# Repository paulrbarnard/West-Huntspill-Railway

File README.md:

# West-Huntspill-Railway
This is a project for the West Huntspill Model Railway

https://en-gb.facebook.com/pages/category/Arts---Entertainment/West-Huntspill-Railway-246006162152817/

WHR run model live steam and electric locos on their track.

This project was to replace the old signal system with something a little more flexible
The key modules are the SignalBox which provides the control logic with a track display
and the sensor/lights module that detects the trains and switches the signal lights.

PCB layouts are included in the PCB folder in KiCAD format. Parts lists and UK suppliers are in the excel files in the PCB section.

An overview manual is contained in the .docx file

The PCB layouts and code are released free of charge and can be used or modified in any way you like.

No expressed or implied warrenty or gaurentee is made.

If you like the project and make use of it consider a donation to the West Huntspill Model Railway

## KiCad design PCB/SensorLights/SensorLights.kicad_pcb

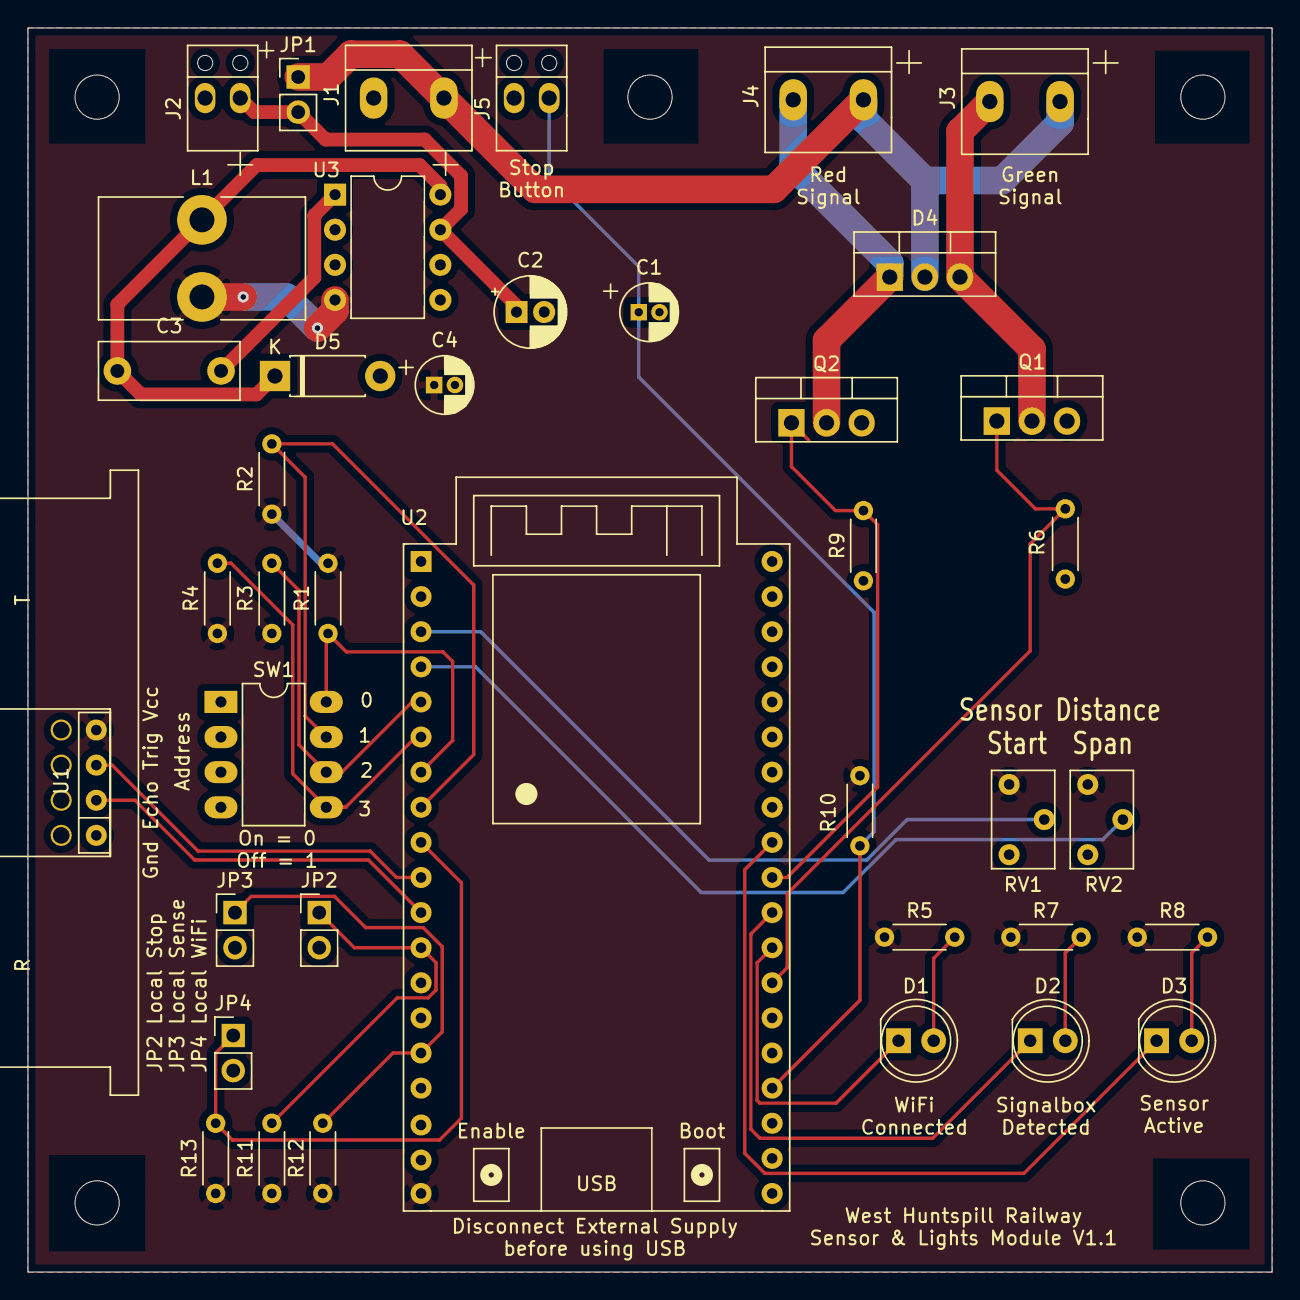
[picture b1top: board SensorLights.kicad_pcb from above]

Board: 2 copper layers, 90.0 x 90.0 mm, 40 parts (0 on the bottom side), 28 nets.

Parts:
C1, C4: 68uF; C_Radial_D4.0mm_H7.0mm_P1.50mm
C2: 100uF; CP_Radial_D5.0mm_P2.00mm
C3: 10nF; C_Rect_L10.0mm_W4.0mm_P7.50mm_MKS4
D1: Yellow; LED_D5.0mm
D2: Green; LED_D5.0mm
D3: Red; LED_D5.0mm
D4: DSSK50-01A; TO-220-3_Vertical
D5: 1N5819RL; D_DO-41_SOD81_P7.62mm_Horizontal
J1: Signal Power; 2WayTerminalStrip_5mm
J2: Board Power; 2WayScrewTerminal_2.54
J3: Green Signal; 2WayTerminalStrip_5mm
J4: Red Signal; 2WayTerminalStrip_5mm
J5: Manual Stop; 2WayScrewTerminal_2.54
JP1: Jumper; PinHeader_1x02_P2.54mm_Vertical
JP2: Local Stop; PinHeader_1x02_P2.54mm_Vertical
JP3: Local Sense; PinHeader_1x02_P2.54mm_Vertical
JP4: Local WiFi; PinHeader_1x02_P2.54mm_Vertical
L1: 47uH; L_Toroid_Vertical_L14.7mm_W8.6mm_P5.58mm_Pulse_KM-1
Q1, Q2: RFP50N06LE; TO-220-3_Vertical
R1, R2, R3, R4, R6, R9, R11, R12, R13: 10K; R_Axial_DIN0204_L3.6mm_D1.6mm_P5.08mm_Horizontal
R5, R8: 1K2; R_Axial_DIN0204_L3.6mm_D1.6mm_P5.08mm_Horizontal
R7, R10: 470R; R_Axial_DIN0204_L3.6mm_D1.6mm_P5.08mm_Horizontal
RV1, RV2: 10K; Potentiometer_TT_M64W
SW1: Address; DIP_SW-8_W7.62mm_LongPads
U1: HC-SR04
U2: ESP32_DevKit_V4; esp32_devkit_v4
U3: LM2675N-5; DIP-8_W7.62mm

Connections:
+5V: C4.1, L1.2, R1.1, R2.1, R3.1, R4.1, R5.1, R7.1, R8.1, R10.1, R11.1, R12.1, R13.1, RV1.1, RV2.1, U1.4, U2.19, U3.4
/5V Supply/6V-24V: C2.1, J2.2, JP1.2, U3.7
GND: C1.2, C2.2, C4.2, D5.2, J1.1, J2.1, J5.1, JP2.2, JP3.2, JP4.2, Q1.3, Q2.3, R6.2, R9.2, RV1.3, RV2.3, SW1.1, SW1.2, SW1.3, SW1.4, U1.1, U2.14, U2.32, U2.38, U3.6
unnamed: C3.1, D5.1, L1.1, U3.8
unnamed: C3.2, U3.1
unnamed: D1.1, U2.27
unnamed: D1.2, R5.2
unnamed: D2.1, U2.28
unnamed: D2.2, R7.2
unnamed: D3.1, U2.30
unnamed: D3.2, R8.2
unnamed: D4.1, J4.1, Q2.2
unnamed: D4.3, J3.1, Q1.2
unnamed: JP2.1, R11.2, U2.12
unnamed: JP3.1, R12.2, U2.15
unnamed: Q1.1, R6.1, U2.26
unnamed: Q2.1, R9.1, U2.29
unnamed: R1.2, SW1.8, U2.7
unnamed: R2.2, SW1.7, U2.8
unnamed: R3.2, SW1.6, U2.5
unnamed: R4.2, SW1.5, U2.6
unnamed: RV1.2, U2.3
unnamed: RV2.2, U2.4
unnamed: U1.2, U2.11
unnamed: U1.3, U2.10
SignalPower: D4.2, J1.2, J3.2, J4.2, JP1.1
Stop: C1.1, J5.2, R10.2, U2.23
lWiFi: JP4.1, R13.2, U2.9

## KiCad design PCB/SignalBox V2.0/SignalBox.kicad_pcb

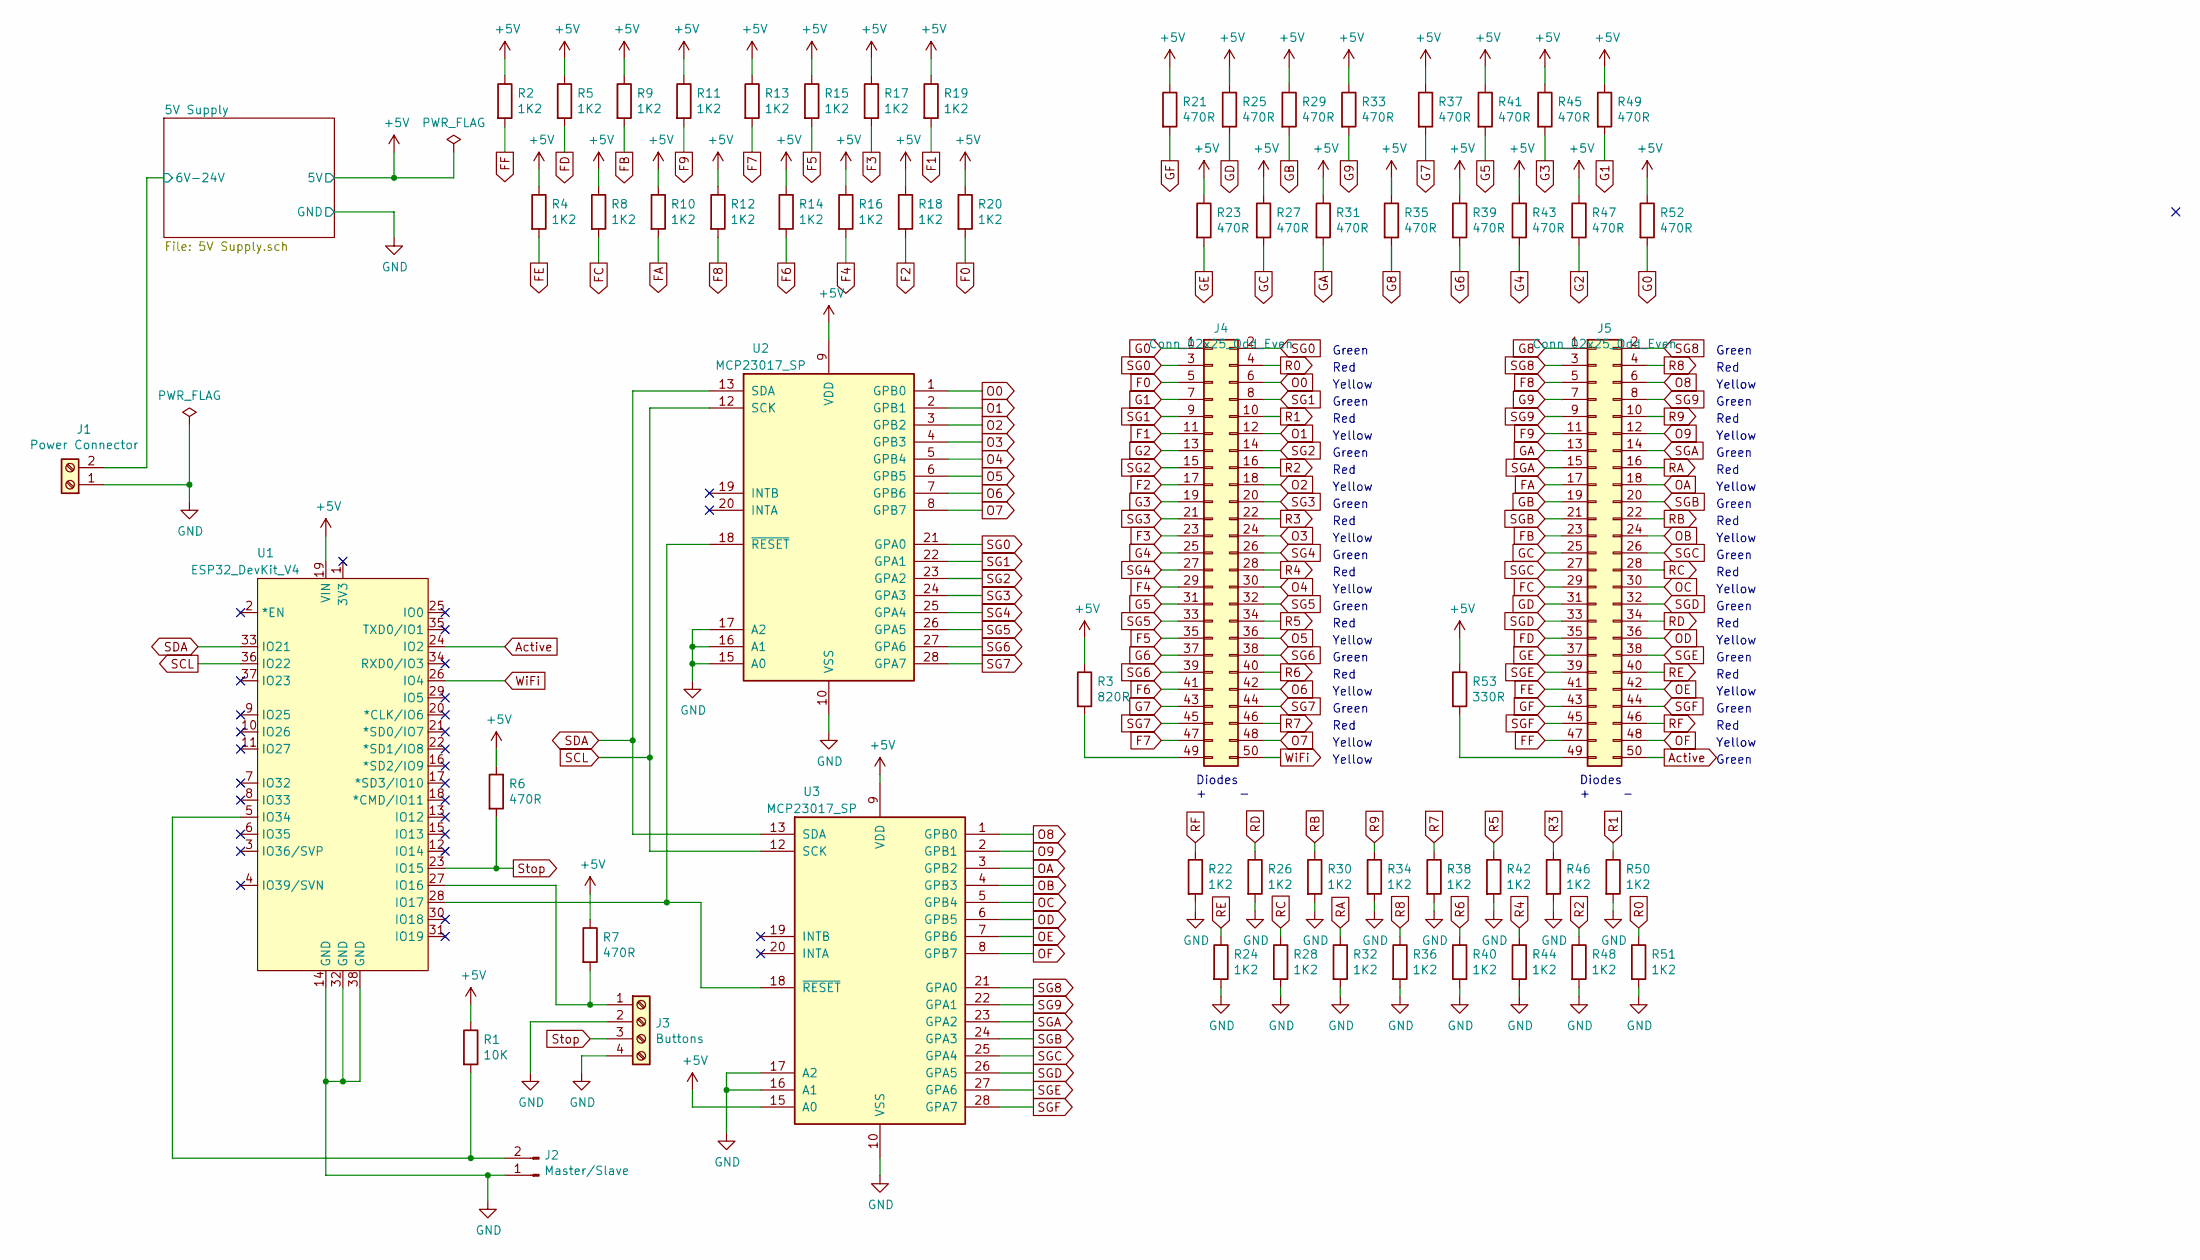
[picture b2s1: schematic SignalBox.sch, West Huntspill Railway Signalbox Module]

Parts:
J1: Power Connector; 2WayScrewTerminal_2.54
J2: Master/Slave; SW_DIP_SPSTx01_Slide_6.7x4.1mm_W7.62mm_P2.54mm_LowProfile
J3: Buttons; 4WayScrewTerminal_2.54mm
J4, J5: Conn_02x25_Odd_Even; IDC-Header_2x25_P2.54mm_Vertical
R1: 10K; R_Axial_DIN0204_L3.6mm_D1.6mm_P5.08mm_Horizontal
R2, R4, R5, R8, R9, R10, R11, R12, R13, R14, R15, R16, R17, R18, R19, R20, R22, R24, R26, R28, R30, R32, R34, R36, R38, R40, R42, R44, R46, R48, R50, R51: 1K2; R_Axial_DIN0204_L3.6mm_D1.6mm_P5.08mm_Horizontal
R3: 820R; R_Axial_DIN0204_L3.6mm_D1.6mm_P5.08mm_Horizontal
R6, R7, R21, R23, R25, R27, R29, R31, R33, R35, R37, R39, R41, R43, R45, R47, R49, R52: 470R; R_Axial_DIN0204_L3.6mm_D1.6mm_P5.08mm_Horizontal
R53: 330R; R_Axial_DIN0204_L3.6mm_D1.6mm_P5.08mm_Horizontal
U1: ESP32_DevKit_V4; esp32_devkit_v4
U2, U3: MCP23017_SP; DIP-28_W7.62mm

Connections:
+5V: R1.1, R2.1, R3.1, R4.1, R5.1, R6.1, R7.1, R8.1, R9.1, R10.1, R11.1, R12.1, R13.1, R14.1, R15.1, R16.1, R17.1, R18.1, R19.1, R20.1, R21.1, R23.1, R25.1, R27.1, R29.1, R31.1, R33.1, R35.1, R37.1, R39.1, R41.1, R43.1, R45.1, R47.1, R49.1, R52.1, R53.1, U1.19 (VIN), U2.9 (VDD), U3.9 (VDD), U3.15 (A0); also elsewhere on the board
/5V Supply/6V-24V: J1.2; also elsewhere on the board
Active: J5.50, U1.24 (IO2)
F0: J4.5, R20.2
F1: J4.11, R19.2
F2: J4.17, R18.2
F3: J4.23, R17.2
F4: J4.29, R16.2
F5: J4.35, R15.2
F6: J4.41, R14.2
F7: J4.47, R13.2
F8: J5.5, R12.2
F9: J5.11, R11.2
FA: J5.17, R10.2
FB: J5.23, R9.2
FC: J5.29, R8.2
FD: J5.35, R5.2
FE: J5.41, R4.2
FF: J5.47, R2.2
G0: J4.1, R52.2
G1: J4.7, R49.2
G2: J4.13, R47.2
G3: J4.19, R45.2
G4: J4.25, R43.2
G5: J4.31, R41.2
G6: J4.37, R39.2
G7: J4.43, R37.2
G8: J5.1, R35.2
G9: J5.7, R33.2
GA: J5.13, R31.2
GB: J5.19, R29.2
GC: J5.25, R27.2
GD: J5.31, R25.2
GE: J5.37, R23.2
GF: J5.43, R21.2
GND: J1.1, J2.1, J3.2, J3.4, R22.2, R24.2, R26.2, R28.2, R30.2, R32.2, R34.2, R36.2, R38.2, R40.2, R42.2, R44.2, R46.2, R48.2, R50.2, R51.2, U1.14 (GND), U1.32 (GND), U1.38 (GND), U2.10 (VSS), U2.15 (A0), U2.16 (A1), U2.17 (A2), U3.10 (VSS), U3.16 (A1), U3.17 (A2); also elsewhere on the board
unnamed: J2.2, R1.2, U1.5 (IO34)
unnamed: J3.1, R7.2, U1.27 (IO16)
unnamed: J4.49, R3.2
unnamed: J5.49, R53.2
unnamed: U1.28 (IO17), U2.18 (~RESET~), U3.18 (~RESET~)
O0: J4.6, U2.1 (GPB0)
O1: J4.12, U2.2 (GPB1)
O2: J4.18, U2.3 (GPB2)
O3: J4.24, U2.4 (GPB3)
O4: J4.30, U2.5 (GPB4)
O5: J4.36, U2.6 (GPB5)
O6: J4.42, U2.7 (GPB6)
O7: J4.48, U2.8 (GPB7)
O8: J5.6, U3.1 (GPB0)
O9: J5.12, U3.2 (GPB1)
OA: J5.18, U3.3 (GPB2)
OB: J5.24, U3.4 (GPB3)
OC: J5.30, U3.5 (GPB4)
OD: J5.36, U3.6 (GPB5)
OE: J5.42, U3.7 (GPB6)
OF: J5.48, U3.8 (GPB7)
R0: J4.4, R51.1
R1: J4.10, R50.1
R2: J4.16, R48.1
R3: J4.22, R46.1
R4: J4.28, R44.1
R5: J4.34, R42.1
R6: J4.40, R40.1
R7: J4.46, R38.1
R8: J5.4, R36.1
R9: J5.10, R34.1
RA: J5.16, R32.1
RB: J5.22, R30.1
RC: J5.28, R28.1
RD: J5.34, R26.1
RE: J5.40, R24.1
RF: J5.46, R22.1
SCL: U1.36 (IO22), U2.12 (SCK), U3.12 (SCK)
SDA: U1.33 (IO21), U2.13 (SDA), U3.13 (SDA)
SG0: J4.2, J4.3, U2.21 (GPA0)
SG1: J4.8, J4.9, U2.22 (GPA1)
SG2: J4.14, J4.15, U2.23 (GPA2)
SG3: J4.20, J4.21, U2.24 (GPA3)
SG4: J4.26, J4.27, U2.25 (GPA4)
SG5: J4.32, J4.33, U2.26 (GPA5)
SG6: J4.38, J4.39, U2.27 (GPA6)
SG7: J4.44, J4.45, U2.28 (GPA7)
SG8: J5.2, J5.3, U3.21 (GPA0)
SG9: J5.8, J5.9, U3.22 (GPA1)
SGA: J5.14, J5.15, U3.23 (GPA2)
SGB: J5.20, J5.21, U3.24 (GPA3)
SGC: J5.26, J5.27, U3.25 (GPA4)
SGD: J5.32, J5.33, U3.26 (GPA5)
SGE: J5.38, J5.39, U3.27 (GPA6)
SGF: J5.44, J5.45, U3.28 (GPA7)
Stop: J3.3, R6.2, U1.23 (IO15)
WiFi: J4.50, U1.26 (IO4)

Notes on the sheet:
Diodes + -
Green
Red
Yellow

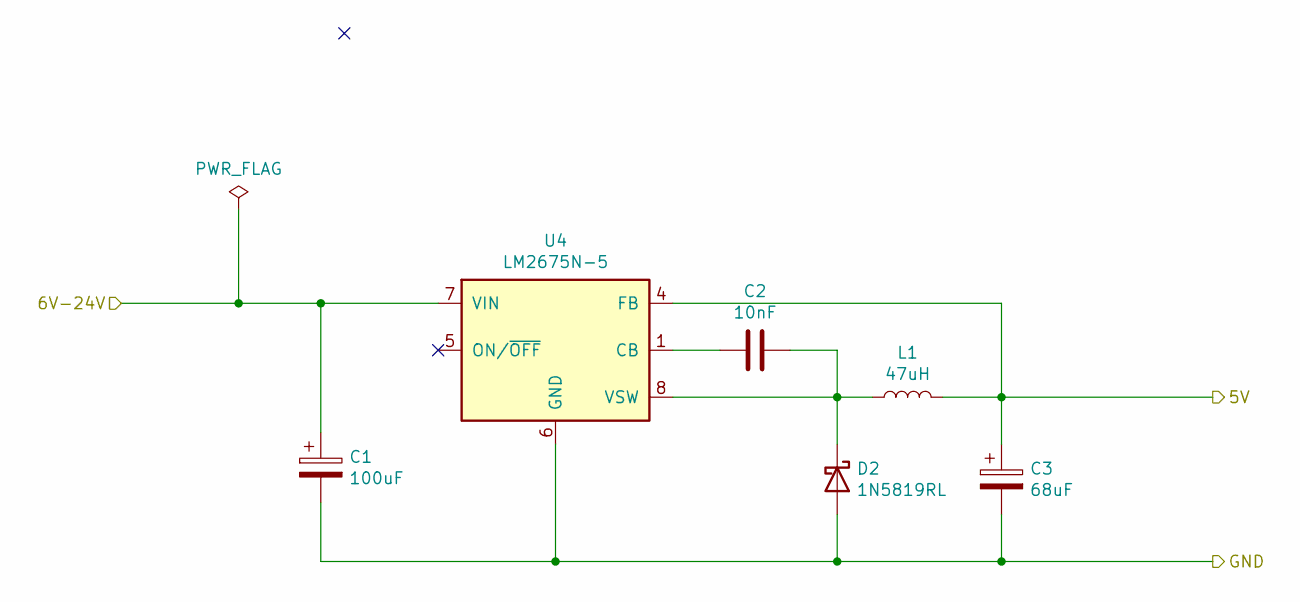
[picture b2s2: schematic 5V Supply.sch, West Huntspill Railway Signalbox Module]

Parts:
C1: 100uF; CP_Radial_D5.0mm_P2.00mm
C2: 10nF; C_Rect_L10.0mm_W4.0mm_P7.50mm_MKS4
C3: 68uF; C_Radial_D4.0mm_H7.0mm_P1.50mm
D2: 1N5819RL; D_DO-41_SOD81_P7.62mm_Horizontal
L1: 47uH; L_Toroid_Vertical_L14.7mm_W8.6mm_P5.58mm_Pulse_KM-1
U4: LM2675N-5; DIP-8_W7.62mm

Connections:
+5V: C3.1, L1.2, U4.4 (FB); also elsewhere on the board
/5V Supply/6V-24V: C1.1, U4.7 (VIN); also elsewhere on the board
GND: C1.2, C3.2, D2.2 (A), U4.6 (GND); also elsewhere on the board
unnamed: C2.1, D2.1 (K), L1.1, U4.8 (VSW)
unnamed: C2.2, U4.1 (CB)

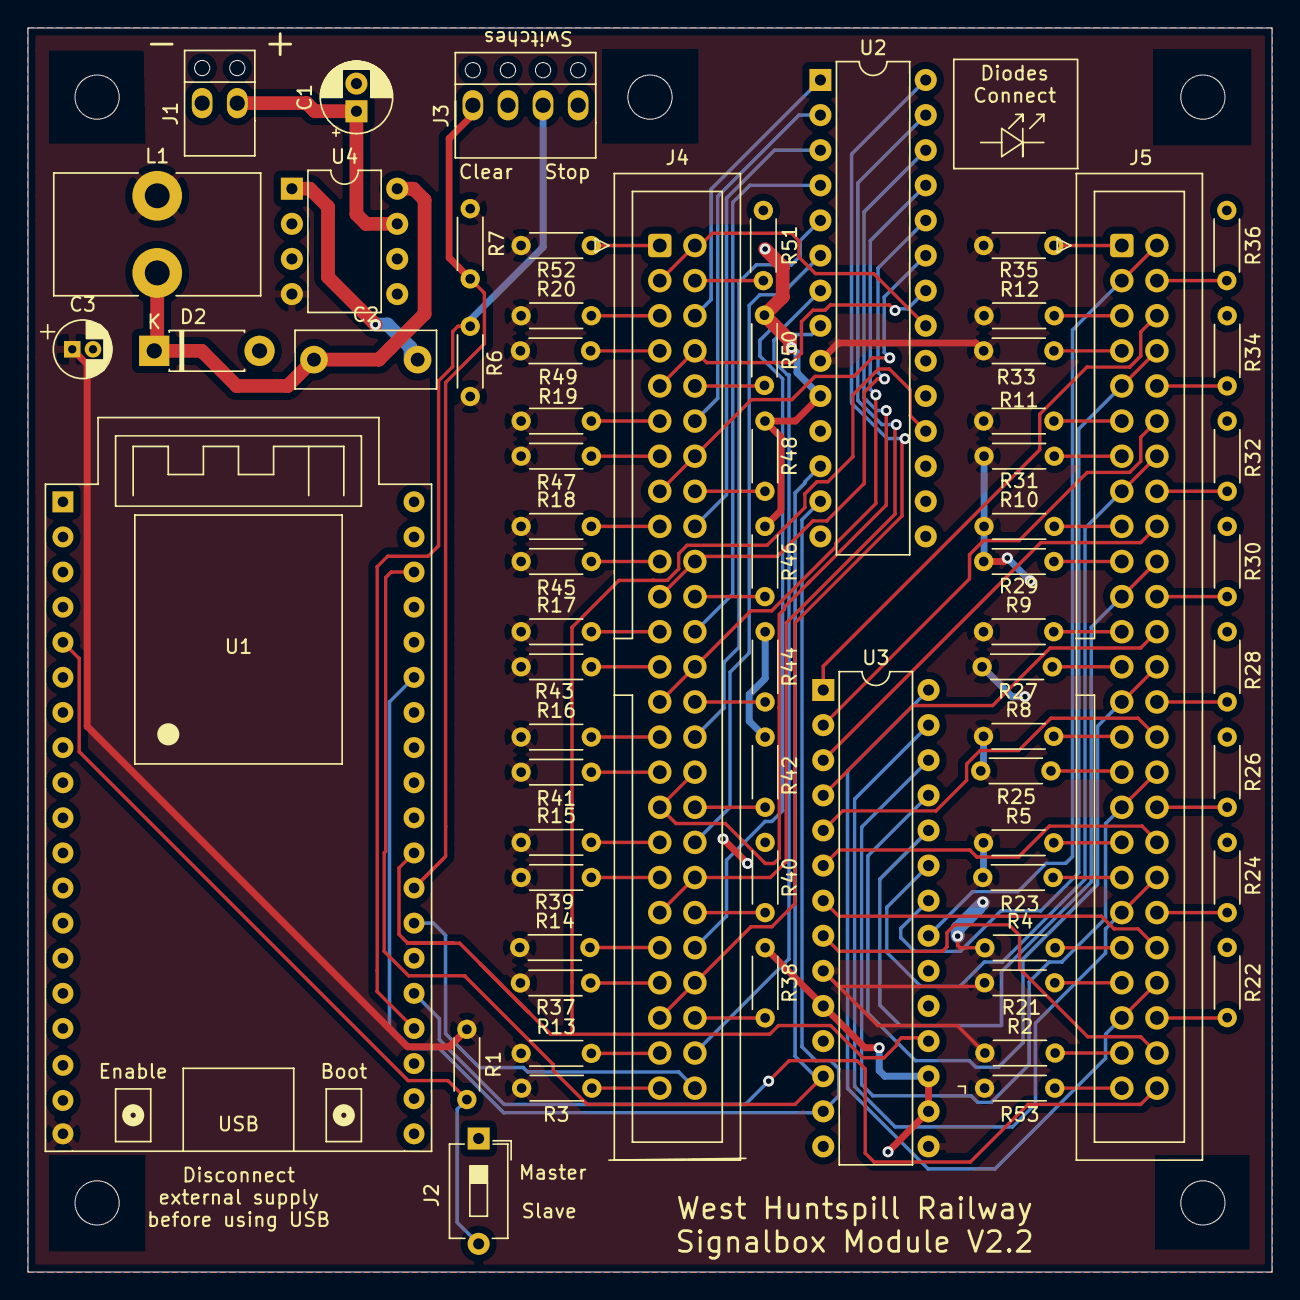
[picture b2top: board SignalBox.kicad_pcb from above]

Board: 2 copper layers, 90.0 x 90.0 mm, 67 parts (0 on the bottom side), 95 nets.

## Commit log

2021-08-05 project settings
2021-08-05 Updated document to include link to this GIT
2021-08-18 Corrected bug in SignalBox slave mode. Had used the master/slave pin define rather than reading the pin...
2021-08-18 added potentiometers for setting of the sensor distance
2021-08-18 Fixed significant issue with light control. A } had got displaced. Added some debug to the signalbox to help find the problem
2021-08-27 Added functionality to the Stop button to support forced track clearing on release of Stop Button. This is to enable use at the Steaming bays where a train is removed from the tracks. Releasing the s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
2021-09-09 Added supportng files such as the face plate art work (including the image files for the iOS and macOS assets). Some CAD files for 3D models used during the development. Added a feature to flash the 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
2021-09-09 Added section about the external WiFi usedto the user manual
2022-03-07 Added support for remote configuration ussing EEPROM in Signalbox. Supports companion application for iOS, macOS and watchOS to configure and control the lights remotely.
2022-03-07 Added WHRDisplay XCode project as submodule
2022-03-07 linked WHRDisplay
2022-03-07 no message

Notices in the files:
PCB/SignalBox V2.0/5V Supply.sch:
creativecommons.org/licenses/by/4.0
License: CC BY 4.0
